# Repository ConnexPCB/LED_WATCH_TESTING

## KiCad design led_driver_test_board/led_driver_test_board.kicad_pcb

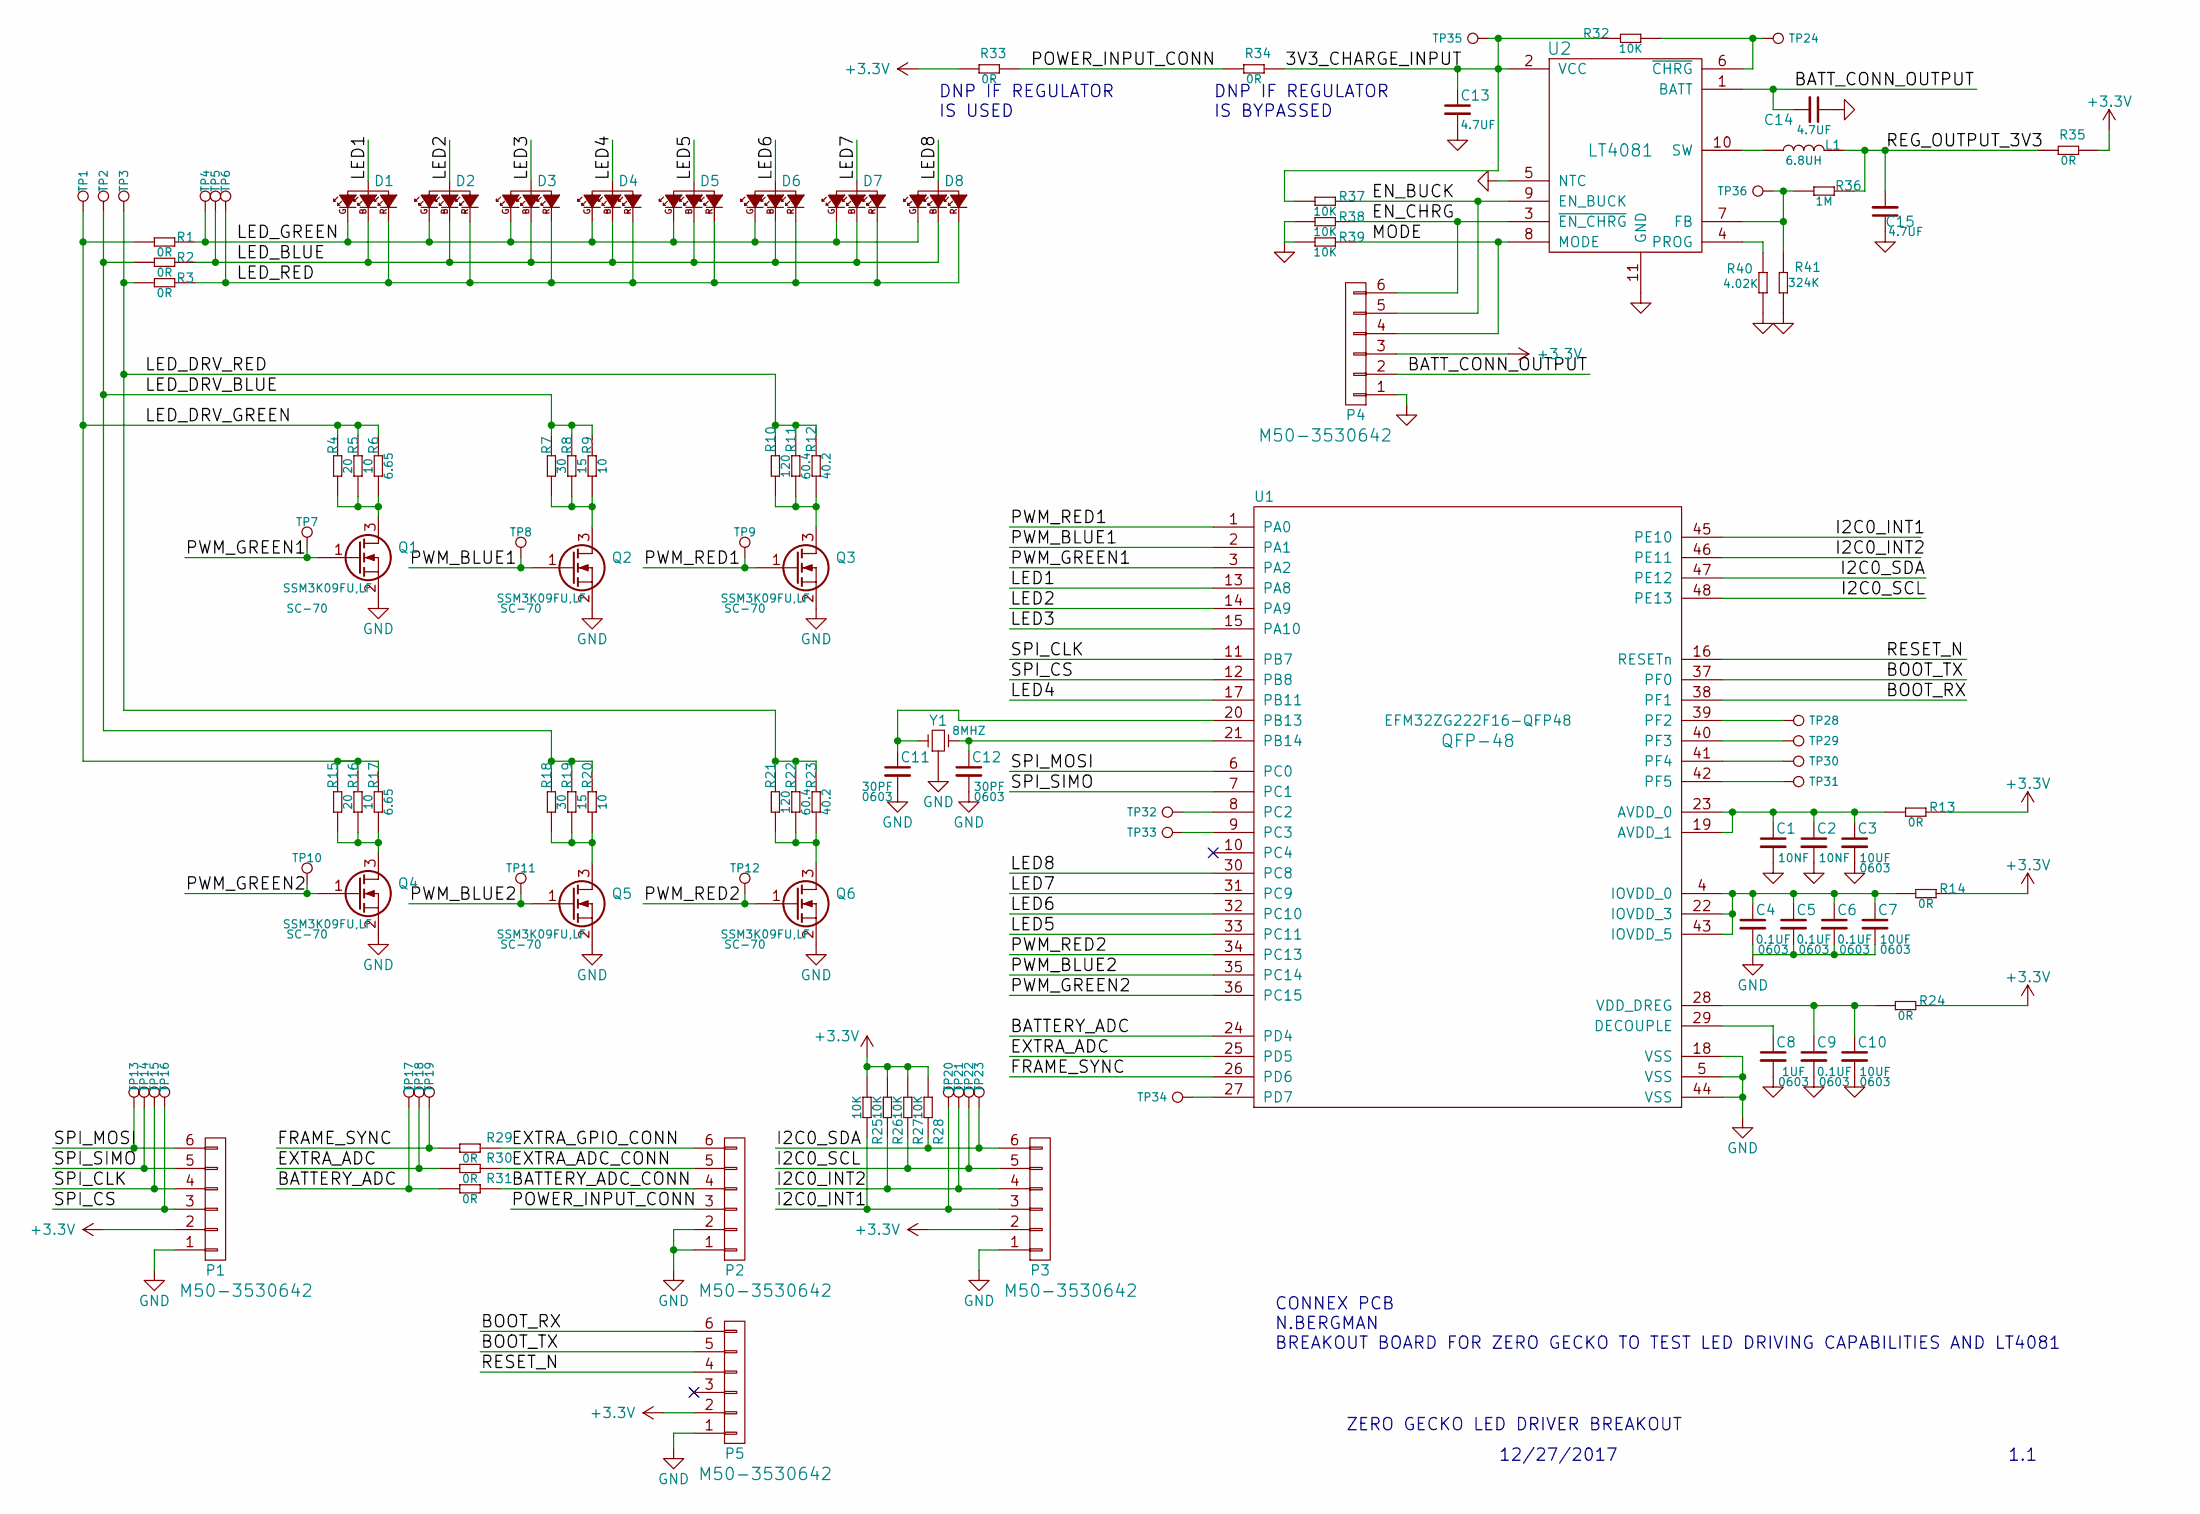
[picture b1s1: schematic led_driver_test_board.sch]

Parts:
C1, C2: CONNEX-SMD-CAP-10NF-0603; C_0603; MPN GRM188R70J103KA01D
C3, C7, C10: connex_cap_10UF_0603_6V3; C_0603; MPN CL10A106KQ8NNNC
C4, C5, C6, C9: connex_cap_100NF_0603_10V; C_0603; MPN C0603C104K8RACTU
C8: connex_cap_1UF_0603_10V; C_0603; MPN C0603C105K8RACTU
C11, C12: connex_cap_30PF_0603_50V; C_0603; MPN GRM1885C1H300JA01D
C13, C14, C15: CONNEX-SMD-CAP-4700NF-0603; C_0603; MPN GRM188R60J475ME19D
D1, D2, D3, D4, D5, D6, D7, D8: LED_RGB_SMLP34RGB1W3; led_0404_SMLP34RGB1W3; MPN SMLP34RGB1W3
L1: CONNEX-SMD-INDUCTOR-6R8M-0603; L_0603; MPN GLFR1608T6R8M-LR
P1, P2, P3, P4, P5: CONN_01X06_M50-3530642; Pin_Header_Straight_1x06; MPN M50-3530642
Q1, Q2, Q3, Q4, Q5, Q6: Q_NMOS_SSM3K09FULF; SC-70; MPN SSM3K09FU,LF
R1, R2, R3, R13, R14, R24, R29, R30, R31, R33, R34, R35: SMD-RES-0R-1_4W_0603_; R_0603; MPN CRCW06030000Z0EAHP
R4, R15: CONNEX-SMD-RES-20-0603; R_0603; MPN CRCW060320R0JNEA
R5, R9, R16, R20: CONNEX-SMD-RES-10-0603; R_0603; MPN RCA060310R0JNEA
R6, R17: CONNEX-SMD-RES-6R65-0603; R_0603; MPN CRCW06036R65FKEA
R7, R18: CONNEX-SMD-RES-30-0603; R_0603; MPN CRCW060330R0JNEA
R8, R19: CONNEX-SMD-RES-15-0603; R_0603; MPN CRCW060315R0JNEA
R10, R21: CONNEX-SMD-RES-120-0603; R_0603; MPN CRCW0603120RJNEA
R11, R22: CONNEX-SMD-RES-60R4-0603; R_0603; MPN CRCW060360R4FKEA
R12, R23: CONNEX-SMD-RES-40R2-0603; R_0603; MPN CRCW060340R2FKEA
R25, R26, R27, R28, R32, R37, R38, R39: SMD-RES-10K-1%-1_10W_0603_; R_0603
R36: CONNEX-SMD-RES-1M-0603; R_0603; MPN RCG06031M00FKEA
R40: CONNEX-SMD-RES-4K02-0603; R_0603; MPN CRCW06034K02FKEA
R41: CONNEX-SMD-RES-324K-0603; R_0603; MPN CRCW0603324KFKEA
TP1, TP2, TP3, TP4, TP5, TP6, TP7, TP8, TP9, TP10, TP11, TP12, TP13, TP14, TP15, TP16, TP17, TP18, TP19, TP20, TP21, TP22, TP23, TP24, TP28, TP29, TP30, TP31, TP32, TP33, TP34, TP35, TP36: test_point_smt; TEST_POINT_SMD_50MIL; MPN na
U1: connex_EFM32ZG222F16-QFP48; TQFP-48_7x7mm_Pitch0.5mm; MPN EFM32ZG222F16-QFP48
U2: CONNEX_REGUL_LT4081; CONNEX_DFN_10PIN_3MMX3MM; MPN LTC4081EDD#PBF
Y1: Crystal_8MHZ_ABM3B-8.000MHZ-B2-T; CONNEX_CRYSTAL_4SMD_32X50; MPN ABM3B-8.000MHZ-B2-T

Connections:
+3V3: P1.2, P3.2, P4.3, P5.2, R13.1, R14.1, R24.1, R25.1, R26.1, R27.1, R28.1, R33.1, R35.2
/3V3_CHARGE_INPUT: C13.1, R32.2, R34.2, R37.2, TP35.1, U2.2 (VCC)
/BATTERY_ADC: R31.1, TP17.1, U1.24 (PD4)
/BATTERY_ADC_CONN: P2.4, R31.2
/BATT_CONN_OUTPUT: C14.2, P4.2, U2.1 (BATT)
/BOOT_RX: P5.6, U1.38 (PF1)
/BOOT_TX: P5.5, U1.37 (PF0)
/EN_BUCK: P4.5, R37.1, U2.9 (EN_BUCK)
/EN_CHRG: P4.6, R38.1, U2.3 (~EN_CHRG~)
/EXTRA_ADC: R30.1, TP18.1, U1.25 (PD5)
/EXTRA_ADC_CONN: P2.5, R30.2
/EXTRA_GPIO_CONN: P2.6, R29.2
/FRAME_SYNC: R29.1, TP19.1, U1.26 (PD6)
/I2C0_INT1: P3.3, R25.2, TP20.1, U1.45 (PE10)
/I2C0_INT2: P3.4, R26.2, TP21.1, U1.46 (PE11)
/I2C0_SCL: P3.5, R27.2, TP22.1, U1.48 (PE13)
/I2C0_SDA: P3.6, R28.2, TP23.1, U1.47 (PE12)
/LED1: D1.1, U1.13 (PA8)
/LED2: D2.1, U1.14 (PA9)
/LED3: D3.1, U1.15 (PA10)
/LED4: D4.1, U1.17 (PB11)
/LED5: D5.1, U1.33 (PC11)
/LED6: D6.1, U1.32 (PC10)
/LED7: D7.1, U1.31 (PC9)
/LED8: D8.1, U1.30 (PC8)
/LED_BLUE: D1.3 (B), D2.3 (B), D3.3 (B), D4.3 (B), D5.3 (B), D6.3 (B), D7.3 (B), D8.3 (B), R2.1, TP5.1
/LED_DRV_BLUE: R2.2, R7.1, R8.1, R9.1, R18.1, R19.1, R20.1, TP2.1
/LED_DRV_GREEN: R1.2, R4.1, R5.1, R6.1, R15.1, R16.1, R17.1, TP1.1
/LED_DRV_RED: R3.2, R10.1, R11.1, R12.1, R21.1, R22.1, R23.1, TP3.1
/LED_GREEN: D1.4 (G), D2.4 (G), D3.4 (G), D4.4 (G), D5.4 (G), D6.4 (G), D7.4 (G), D8.4 (G), R1.1, TP4.1
/LED_RED: D1.2 (R), D2.2 (R), D3.2 (R), D4.2 (R), D5.2 (R), D6.2 (R), D7.2 (R), D8.2 (R), R3.1, TP6.1
/MODE: P4.4, R39.1, U2.8 (MODE)
/POWER_INPUT_CONN: P2.3, R33.2, R34.1
/PWM_BLUE1: Q2.1 (G), TP8.1, U1.2 (PA1)
/PWM_BLUE2: Q5.1 (G), TP11.1, U1.35 (PC14)
/PWM_GREEN1: Q1.1 (G), TP7.1, U1.3 (PA2)
/PWM_GREEN2: Q4.1 (G), TP10.1, U1.36 (PC15)
/PWM_RED1: Q3.1 (G), TP9.1, U1.1 (PA0)
/PWM_RED2: Q6.1 (G), TP12.1, U1.34 (PC13)
/REG_OUTPUT_3V3: C15.2, L1.2, R35.1, R36.2
/RESET_N: P5.4, U1.16 (RESETn)
/SPI_CLK: P1.4, TP15.1, U1.11 (PB7)
/SPI_CS: P1.3, TP16.1, U1.12 (PB8)
/SPI_MOSI: P1.6, TP13.1, U1.6 (PC0)
/SPI_SIMO: P1.5, TP14.1, U1.7 (PC1)
GND: C1.2, C2.2, C3.2, C4.2, C5.2, C6.2, C7.2, C8.2, C9.2, C10.2, C11.2, C12.2, C13.2, C14.1, C15.1, P1.1, P2.1, P2.2, P3.1, P4.1, P5.1, Q1.2 (S), Q2.2 (S), Q3.2 (S), Q4.2 (S), Q5.2 (S), Q6.2 (S), R38.2, R39.2, R40.1, R41.2, U1.5 (VSS), U1.18 (VSS), U1.44 (VSS), U2.5 (NTC), U2.11 (GND), Y1.2 (GND), Y1.4 (GND)
unnamed: C1.1, C2.1, C3.1, R13.2, U1.19 (AVDD_1), U1.23 (AVDD_0)
unnamed: C4.1, C5.1, C6.1, C7.1, R14.2, U1.4 (IOVDD_0), U1.22 (IOVDD_3), U1.43 (IOVDD_5)
unnamed: C8.1, U1.29 (DECOUPLE)
unnamed: C9.1, C10.1, R24.2, U1.28 (VDD_DREG)
unnamed: C11.1, U1.20 (PB13), Y1.1
unnamed: C12.1, U1.21 (PB14), Y1.3
unnamed: L1.1, U2.10 (SW)
unnamed: Q1.3 (D), R4.2, R5.2, R6.2
unnamed: Q2.3 (D), R7.2, R8.2, R9.2
unnamed: Q3.3 (D), R10.2, R11.2, R12.2
unnamed: Q4.3 (D), R15.2, R16.2, R17.2
unnamed: Q5.3 (D), R18.2, R19.2, R20.2
unnamed: Q6.3 (D), R21.2, R22.2, R23.2
unnamed: R32.1, TP24.1, U2.6 (~CHRG~)
unnamed: R36.1, R41.1, TP36.1, U2.7 (FB)
unnamed: R40.2, U2.4 (PROG)
unnamed: TP28.1, U1.39 (PF2)
unnamed: TP29.1, U1.40 (PF3)
unnamed: TP30.1, U1.41 (PF4)
unnamed: TP31.1, U1.42 (PF5)
unnamed: TP32.1, U1.8 (PC2)
unnamed: TP33.1, U1.9 (PC3)
unnamed: TP34.1, U1.27 (PD7)

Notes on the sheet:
DNP IF REGULATOR IS USED
DNP IF REGULATOR IS BYPASSED
ZERO GECKO LED DRIVER BREAKOUT
1.1
12/27/2017
CONNEX PCB N.BERGMAN BREAKOUT BOARD FOR ZERO GECKO TO TEST LED DRIVING CAPABILITIES AND LT4081

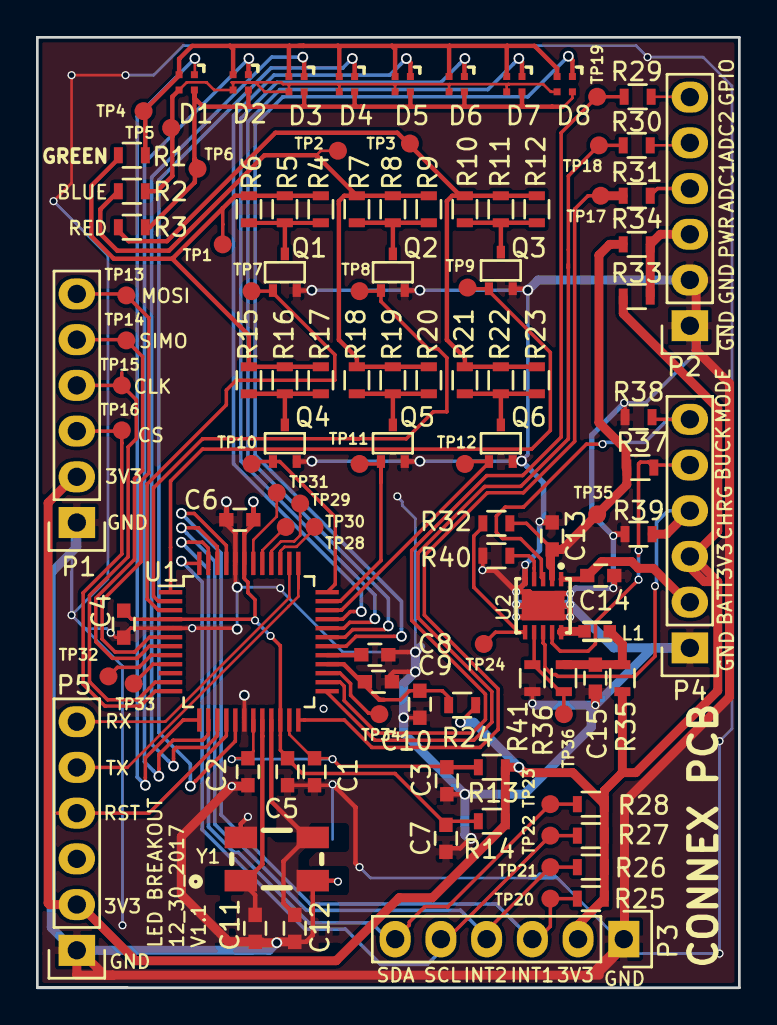
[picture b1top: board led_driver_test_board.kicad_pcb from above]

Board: 2 copper layers, 39.0 x 52.8 mm, 112 parts (0 on the bottom side), 69 nets.

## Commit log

2017-12-05 Created project with led and lt3092
2017-12-06 Added leds, and three current source types to schematic
2017-12-07 Add mcu and routed signals to pins
2017-12-08 Added bulk caps to zero gecko
2017-12-08 First netlist import
2017-12-08 added connex_kicad_libs module
2017-12-08 Added README
2017-12-08 set up local reference for libary files
2017-12-08 Initial routing
2017-12-08 updated lib files
2017-12-09 Added teset points, caps, headers to the schematic
2017-12-09 Updated library files
2017-12-09 Added crystal and some changes to connector pinout. Continued routing pcb
2017-12-09 Updated schematic library files in an attempt to create a library standard
2017-12-09 Updated some library components
2017-12-09 Added regulator to schematic. Routed regulator on board. Adjusted headers
2017-12-10 Minor changes to schematic
2017-12-10 Updated placeholder resistors in schematic
2017-12-10 Changed boot tx/rx on connector. Annotated
2017-12-10 Added 1uF capacitor to the library
2017-12-10 Added 30pF capacitor to library
2017-12-10 Finished first round of routing, passes DRC
2017-12-10 Netlist change
2017-12-10 Replaced R35 with correct BOM
2017-12-10 Added logo and rev info to silkscreen
2017-12-28 Minor changes
2017-12-29 Version 1.1 - Unreveiwed - updated footprints for leds, crystal regulator, general layout, font sizes for labels
2017-12-29 Updated title block to current revision 1.1
